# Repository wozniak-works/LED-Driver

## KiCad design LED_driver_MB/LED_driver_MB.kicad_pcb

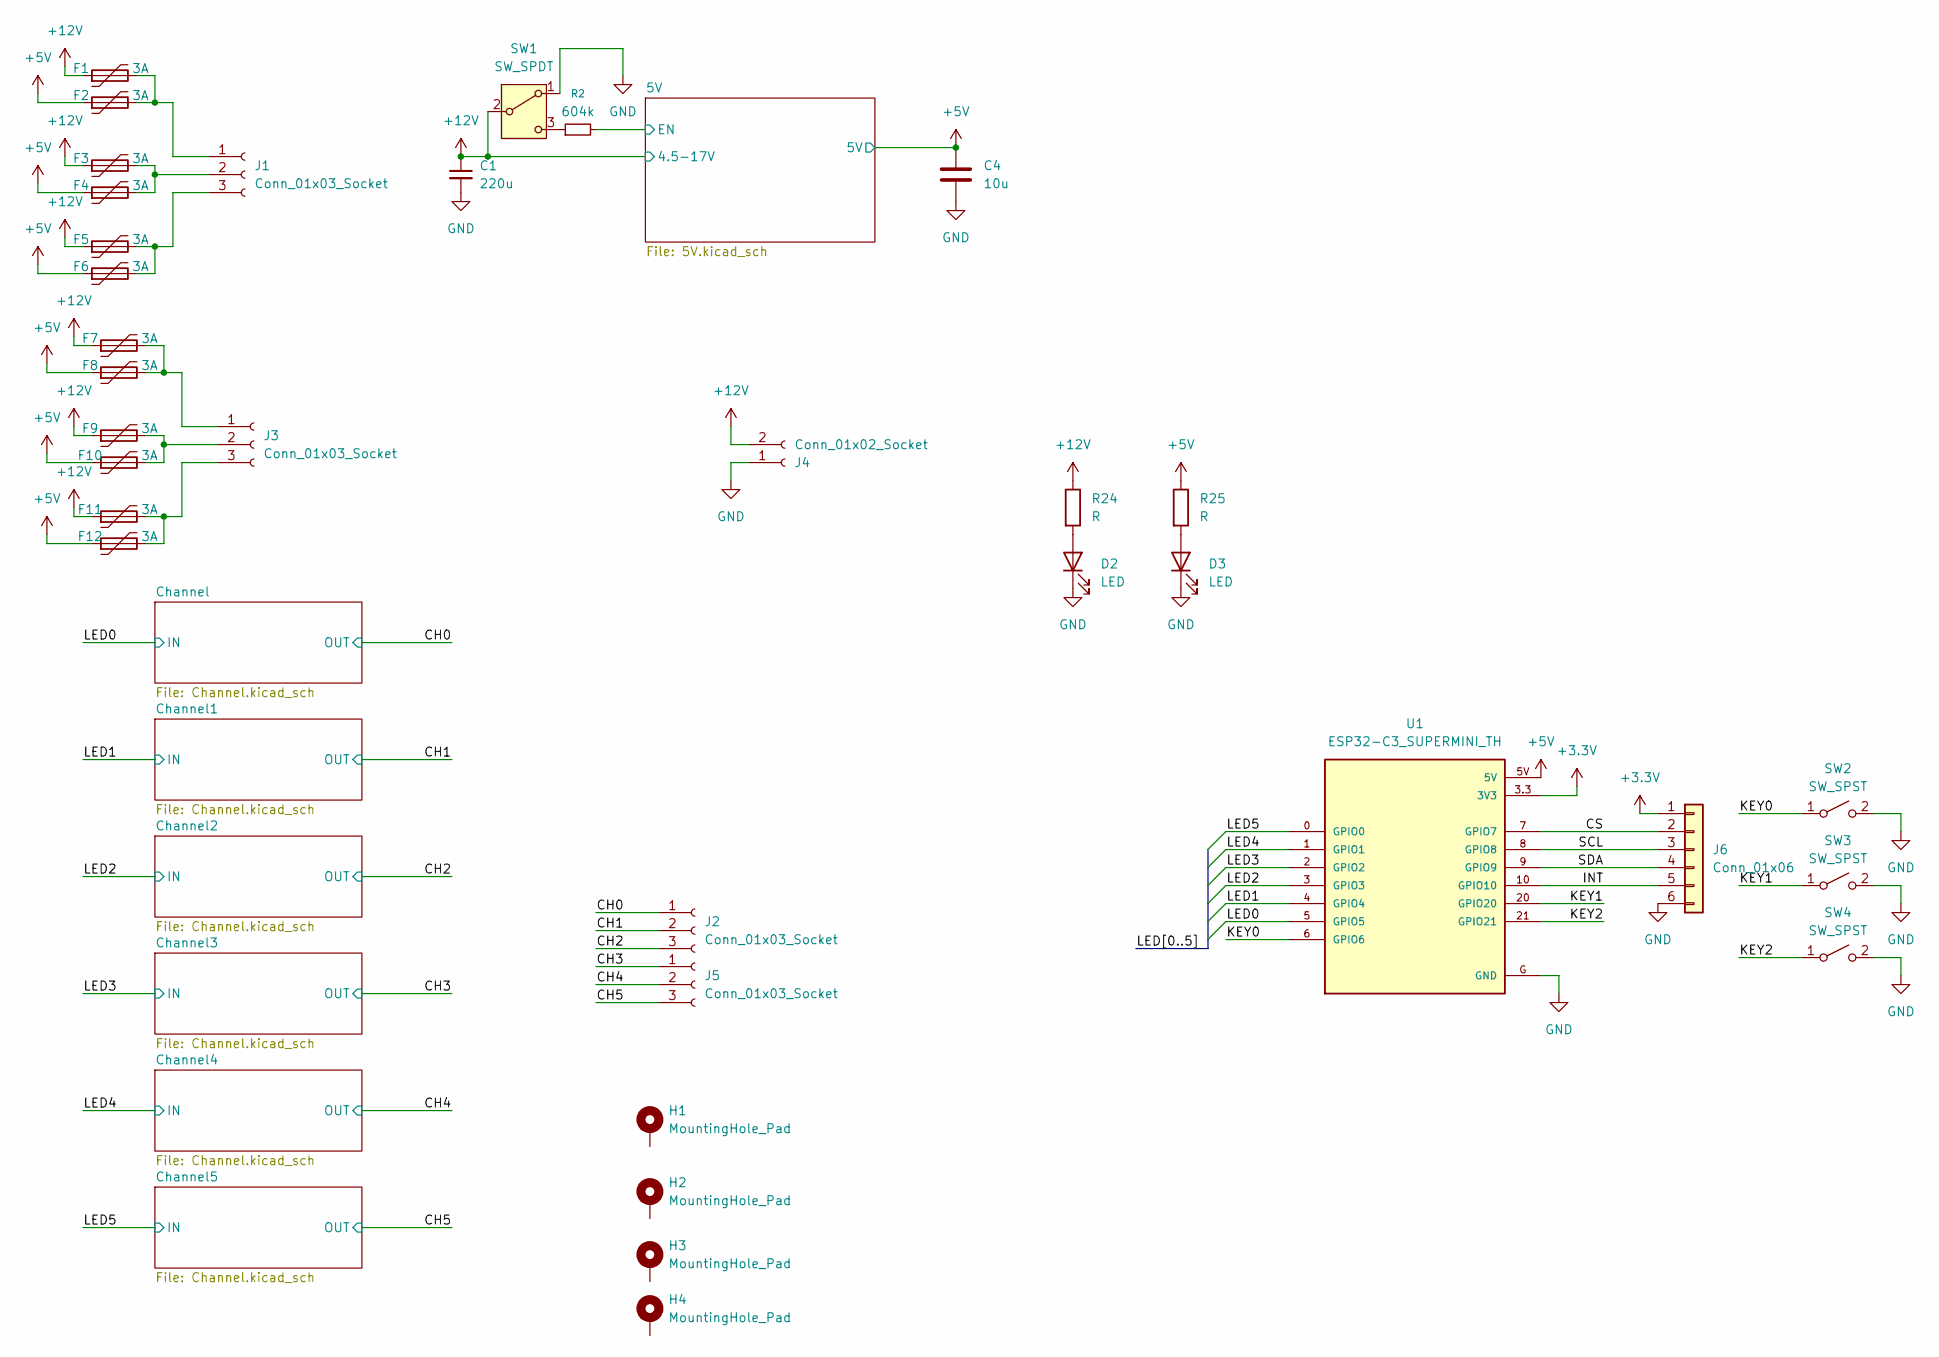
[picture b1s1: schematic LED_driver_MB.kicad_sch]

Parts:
C1: 220u; C_Radial_D8.0mm_H11.5mm_P3.50mm
C4: 10u; C_1206_3216Metric
D2, D3: LED; LED_0603_1608Metric
F1, F2, F3, F4, F5, F6, F7, F8, F9, F10, F11, F12: 3A; Fuse_1812_4532Metric
H1, H2, H3, H4: MountingHole_Pad; MountingHole_2.2mm_M2_Pad_Via
J1, J2, J3, J5: Conn_01x03_Socket; TerminalBlock_bornier-3_P5.08mm
J4: Conn_01x02_Socket; TerminalBlock_bornier-2_P5.08mm
J6: Conn_01x06; PinHeader_1x06_P2.54mm_Vertical
R2: 604k; R_0603_1608Metric
R24, R25: R; R_0603_1608Metric
SW1: SW_SPDT; SW_SPDT_PCM12
SW2, SW3, SW4: SW_SPST; SW_Cherry_MX_PCB_1.00u
U1: ESP32-C3_SUPERMINI_TH; MODULE_ESP32-C3_SUPERMINI_TH

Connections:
+3.3V: J6.1, U1.3.3 (3V3)
+5V: C4.1, F2.1, F4.1, F6.1, F8.1, F10.1, F12.1, R25.1, U1.5V; also elsewhere on the board
+12V: C1.1, F1.1, F3.1, F5.1, F7.1, F9.1, F11.1, J4.2, R24.1, SW1.2 (B); also elsewhere on the board
/5V/EN: R2.2; also elsewhere on the board
/CH0: J2.1; also elsewhere on the board
/CH1: J2.2; also elsewhere on the board
/CH2: J2.3; also elsewhere on the board
/CH3: J5.1; also elsewhere on the board
/CH4: J5.2; also elsewhere on the board
/CH5: J5.3; also elsewhere on the board
/CS: J6.2, U1.7 (GPIO7)
/INT: J6.5, U1.10 (GPIO10)
/KEY0: SW2.1 (A), U1.6 (GPIO6)
/KEY1: SW3.1 (A), U1.20 (GPIO20)
/KEY2: SW4.1 (A), U1.21 (GPIO21)
/LED0: U1.5 (GPIO5); also elsewhere on the board
/LED1: U1.4 (GPIO4); also elsewhere on the board
/LED2: U1.3 (GPIO3); also elsewhere on the board
/LED3: U1.2 (GPIO2); also elsewhere on the board
/LED4: U1.1 (GPIO1); also elsewhere on the board
/LED5: U1.0 (GPIO0); also elsewhere on the board
/SCL: J6.3, U1.8 (GPIO8)
/SDA: J6.4, U1.9 (GPIO9)
GND: C1.2, C4.2, D2.1 (K), D3.1 (K), J4.1, J6.6, SW1.1 (A), SW2.2 (B), SW3.2 (B), SW4.2 (B), U1.G (GND); also elsewhere on the board
unnamed: D2.2 (A), R24.2
unnamed: D3.2 (A), R25.2
unnamed: F1.2, F2.2, J1.1
unnamed: F3.2, F4.2, J1.2
unnamed: F5.2, F6.2, J1.3
unnamed: F7.2, F8.2, J3.1
unnamed: F9.2, F10.2, J3.2
unnamed: F11.2, F12.2, J3.3
unnamed: R2.1, SW1.3 (C)

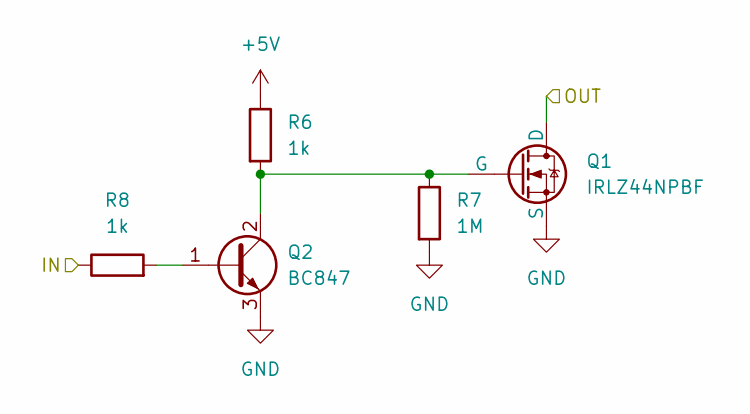
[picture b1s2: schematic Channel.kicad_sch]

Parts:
Q1: IRLZ44NPBF; TO-220-3_Horizontal_TabDown
Q2: BC847; SOT-23
R6, R8: 1k; R_0603_1608Metric; Manufacturer_Part_Number RC0603FR-071KL
R7: 1M; R_0603_1608Metric

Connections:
+5V: R6.1; also elsewhere on the board
/CH0: Q1.1 (D); also elsewhere on the board
/LED0: R8.1; also elsewhere on the board
GND: Q1.3 (S), Q2.3 (E), R7.2; also elsewhere on the board
unnamed: Q1.2 (G), Q2.2 (C), R6.2, R7.1
unnamed: Q2.1 (B), R8.2

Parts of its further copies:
Q3, Q5, Q7, Q9, Q11: IRLZ44NPBF; TO-220-3_Horizontal_TabDown
Q4, Q6, Q8, Q10, Q12: BC847; SOT-23
R9, R11, R12, R14, R15, R17, R18, R20, R21, R23: 1k; R_0603_1608Metric; Manufacturer_Part_Number RC0603FR-071KL
R10, R13, R16, R19, R22: 1M; R_0603_1608Metric

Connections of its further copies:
+5V: R9.1, R12.1, R15.1, R18.1, R21.1; also elsewhere on the board
/CH1: Q3.1 (D); also elsewhere on the board
/CH2: Q5.1 (D); also elsewhere on the board
/CH3: Q7.1 (D); also elsewhere on the board
/CH4: Q9.1 (D); also elsewhere on the board
/CH5: Q11.1 (D); also elsewhere on the board
/LED1: R11.1; also elsewhere on the board
/LED2: R14.1; also elsewhere on the board
/LED3: R17.1; also elsewhere on the board
/LED4: R20.1; also elsewhere on the board
/LED5: R23.1; also elsewhere on the board
GND: Q3.3 (S), Q4.3 (E), Q5.3 (S), Q6.3 (E), Q7.3 (S), Q8.3 (E), Q9.3 (S), Q10.3 (E), Q11.3 (S), Q12.3 (E), R10.2, R13.2, R16.2, R19.2, R22.2; also elsewhere on the board
unnamed: Q3.2 (G), Q4.2 (C), R9.2, R10.1
unnamed: Q4.1 (B), R11.2
unnamed: Q5.2 (G), Q6.2 (C), R12.2, R13.1
unnamed: Q6.1 (B), R14.2
unnamed: Q7.2 (G), Q8.2 (C), R15.2, R16.1
unnamed: Q8.1 (B), R17.2
unnamed: Q10.1 (B), R20.2
unnamed: Q9.2 (G), Q10.2 (C), R18.2, R19.1
unnamed: Q11.2 (G), Q12.2 (C), R21.2, R22.1
unnamed: Q12.1 (B), R23.2

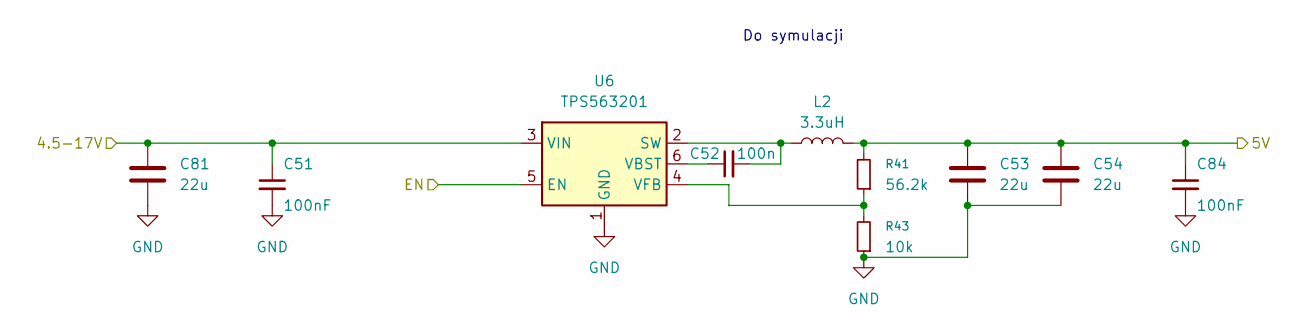
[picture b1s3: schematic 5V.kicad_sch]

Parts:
C51, C84: 100nF; C_0603_1608Metric_Pad1.08x0.95mm_HandSolder; LCSC C1525
C52: 100n; C_0603_1608Metric; Manufacturer_Part_Number GMK107BJ105KA-T
C53, C54, C81: 22u; C_1206_3216Metric
L2: 3.3uH; L_Wuerth_HCM-1350
R41: 56.2k; R_0603_1608Metric
R43: 10k; R_0603_1608Metric
U6: TPS563201; SOT-23-6

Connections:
+5V: C53.1, C54.1, C84.1, L2.2, R41.2; also elsewhere on the board
+12V: C51.1, C81.1, U6.3 (VIN); also elsewhere on the board
/5V/EN: U6.5 (EN); also elsewhere on the board
GND: C51.2, C53.2, C54.2, C81.2, C84.2, R43.1, U6.1 (GND); also elsewhere on the board
unnamed: C52.2, L2.1, U6.2 (SW)
unnamed: C52.1, U6.6 (VBST)
unnamed: R41.1, R43.2, U6.4 (VFB)

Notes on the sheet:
Do symulacji

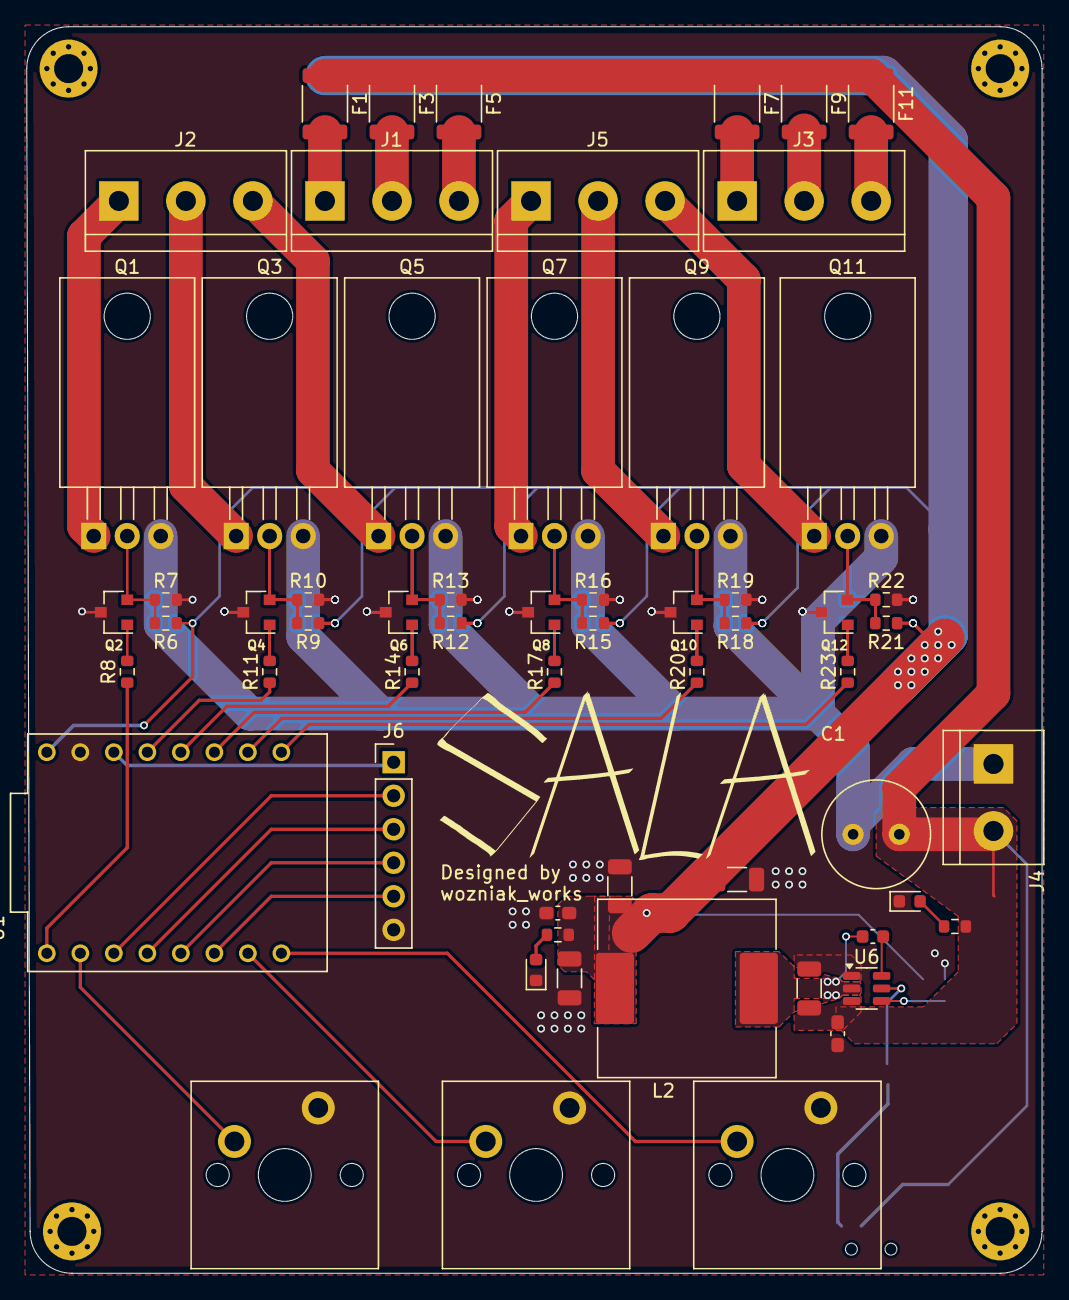
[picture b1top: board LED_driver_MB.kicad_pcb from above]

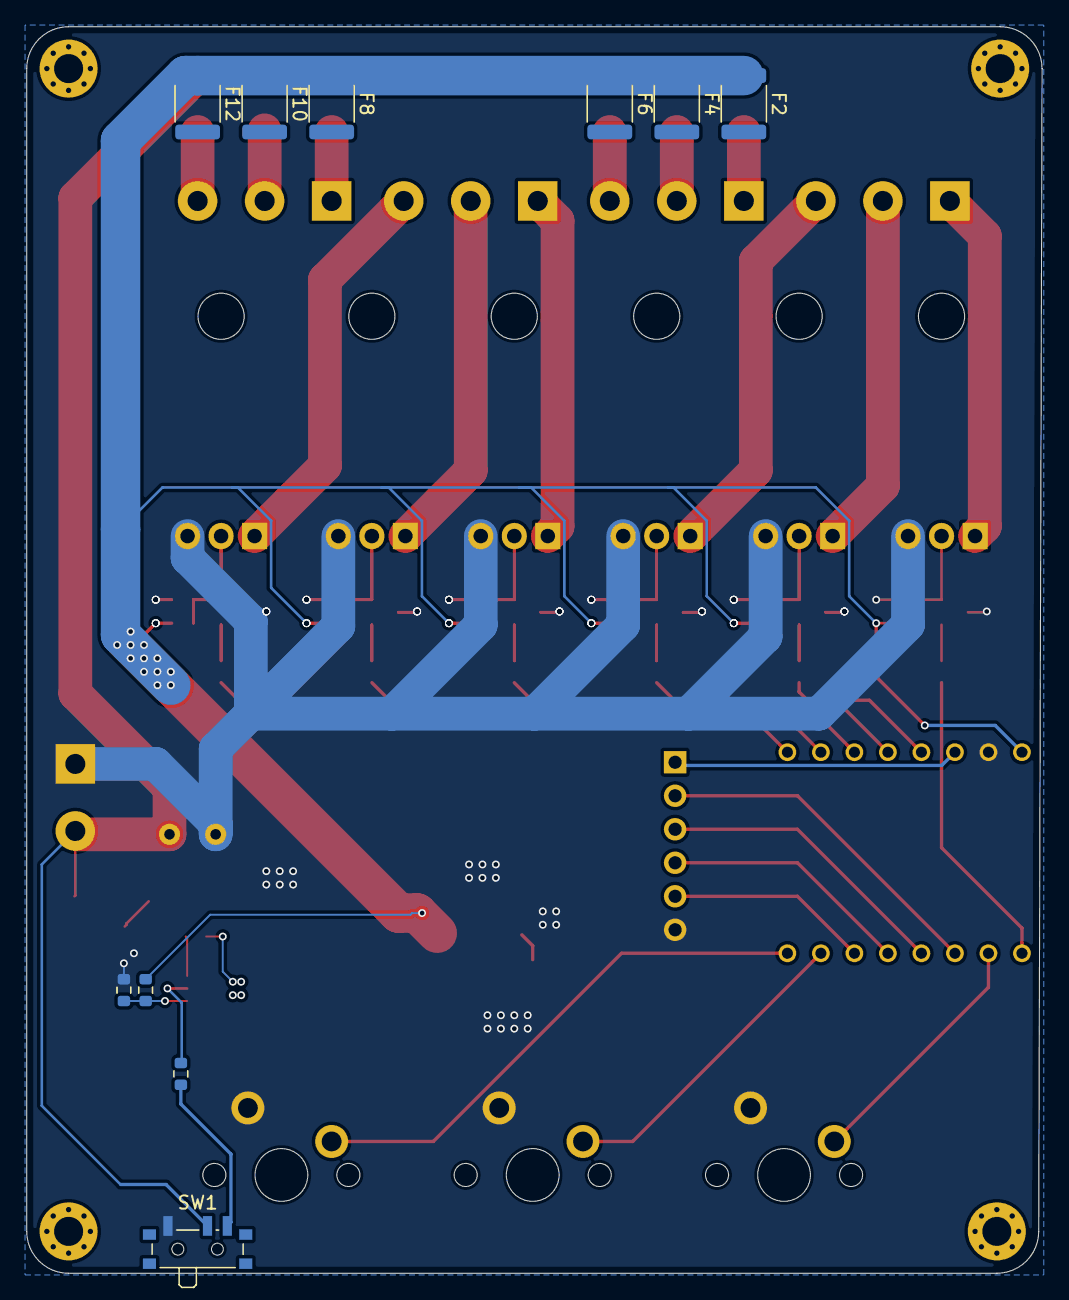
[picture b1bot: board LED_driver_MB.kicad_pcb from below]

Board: 2 copper layers, 77.0 x 94.5 mm, 74 parts (10 on the bottom side), 48 nets.

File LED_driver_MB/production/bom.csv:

Designator,Footprint,Quantity,Value,LCSC Part #
C1,C_Radial_D8.0mm_H11.5mm_P3.50mm,1,220u,
C4,1206,1,10u,
"C51, C84",0603,2,100nF,C1525
C52,0603,1,100n,
"C53, C54, C81",1206,3,22u,
"D2, D3",0603,2,LED,
"F1, F10, F11, F12, F2, F3, F4, F5, F6, F7, F8, F9",1812,12,3A,
"J1, J2, J3, J5",TerminalBlock_bornier-3_P5.08mm,4,Conn_01x03_Socket,
J4,TerminalBlock_bornier-2_P5.08mm,1,Conn_01x02_Socket,
J6,PinHeader_1x06_P2.54mm_Vertical,1,Conn_01x06,
L2,L_Wuerth_HCM-1350,1,3.3uH,
"Q1, Q11, Q3, Q5, Q7, Q9",TO-220-3_Horizontal_TabDown,6,IRLZ44NPBF,
"Q10, Q12, Q2, Q4, Q6, Q8",SOT-23,6,BC847,
"R10, R13, R16, R19, R22, R7",0603,6,1M,
"R11, R12, R14, R15, R17, R18, R20, R21, R23, R6, R8, R9",0603,12,1k,
R2,0603,1,604k,
"R24, R25",0603,2,R,
R41,0603,1,56.2k,
R43,0603,1,10k,
SW1,SW_SPDT_PCM12,1,SW_SPDT,
"SW2, SW3, SW4",SW_Cherry_MX_PCB_1.00u,3,SW_SPST,
U1,MODULE_ESP32-C3_SUPERMINI_TH,1,ESP32-C3_SUPERMINI_TH,
U6,SOT-23-6,1,TPS563201,

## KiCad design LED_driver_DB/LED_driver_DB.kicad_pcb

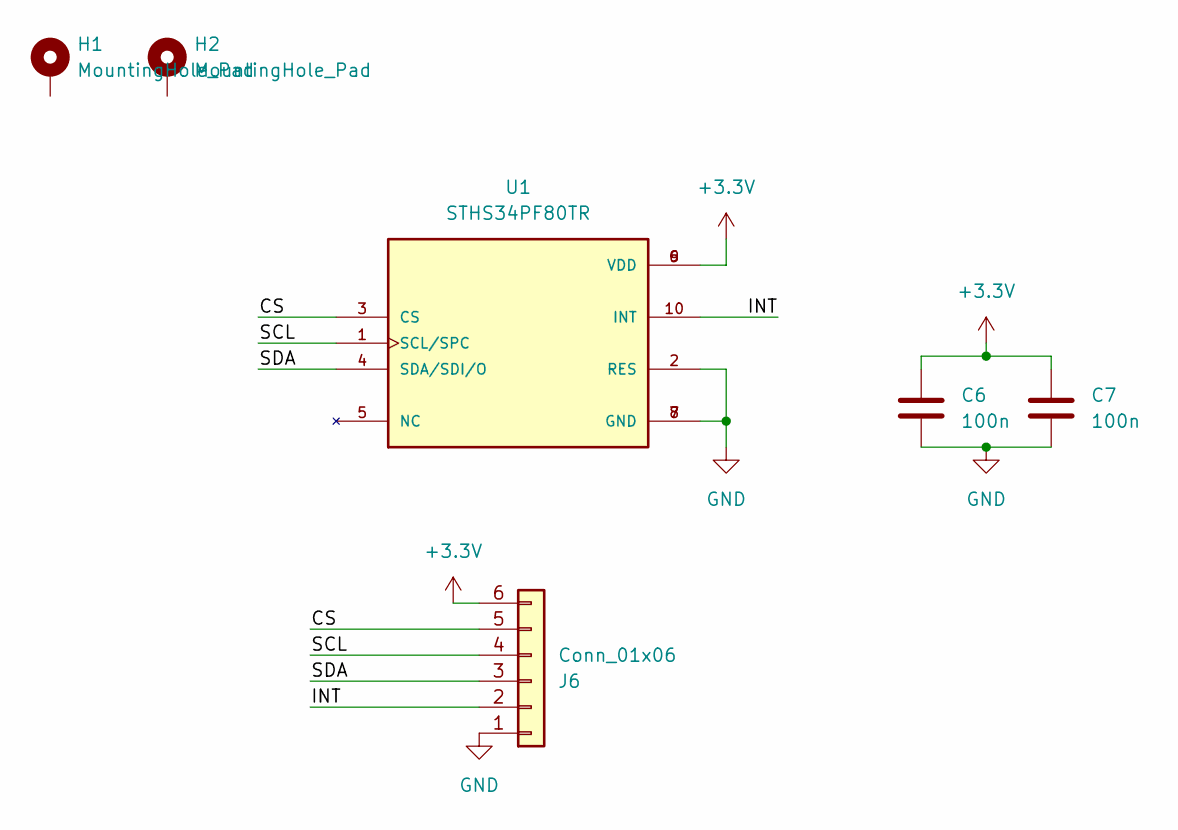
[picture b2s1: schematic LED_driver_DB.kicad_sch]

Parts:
C6, C7: 100n; C_0603_1608Metric; Manufacturer_Part_Number CL10B104KC8NNNC
H1, H2: MountingHole_Pad; MountingHole_2.2mm_M2_Pad_Via
J6: Conn_01x06; PinHeader_1x06_P2.54mm_Vertical
U1: STHS34PF80TR; XDCR_STHS34PF80TR; PARTREV 2

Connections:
+3.3V: C6.1, C7.1, J6.6, U1.6 (VDD), U1.9 (VDD)
/CS: J6.5, U1.3 (CS)
/INT: J6.2, U1.10 (INT)
/SCL: J6.4, U1.1 (SCL/SPC)
/SDA: J6.3, U1.4 (SDA/SDI/O)
GND: C6.2, C7.2, J6.1, U1.2 (RES), U1.7 (GND), U1.8 (GND)

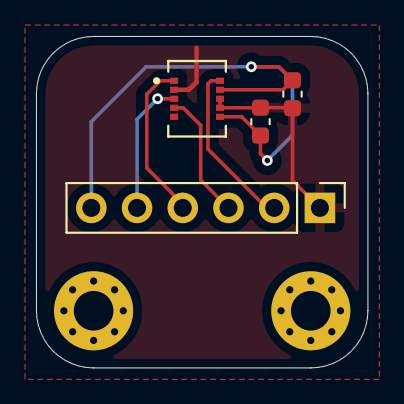
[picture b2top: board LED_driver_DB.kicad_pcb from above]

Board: 2 copper layers, 18.4 x 18.4 mm, 6 parts (0 on the bottom side), 6 nets.

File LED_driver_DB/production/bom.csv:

Designator,Footprint,Quantity,Value,LCSC Part #
"C6, C7",0603,2,100n,
J6,PinHeader_1x06_P2.54mm_Vertical,1,Conn_01x06,
U1,XDCR_STHS34PF80TR,1,STHS34PF80TR,

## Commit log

2026-03-24 Added all files
2026-04-13 add LICENSE file
2026-04-15 change buck converter to TPS563201, production files generated
2026-04-17 Via size unified
